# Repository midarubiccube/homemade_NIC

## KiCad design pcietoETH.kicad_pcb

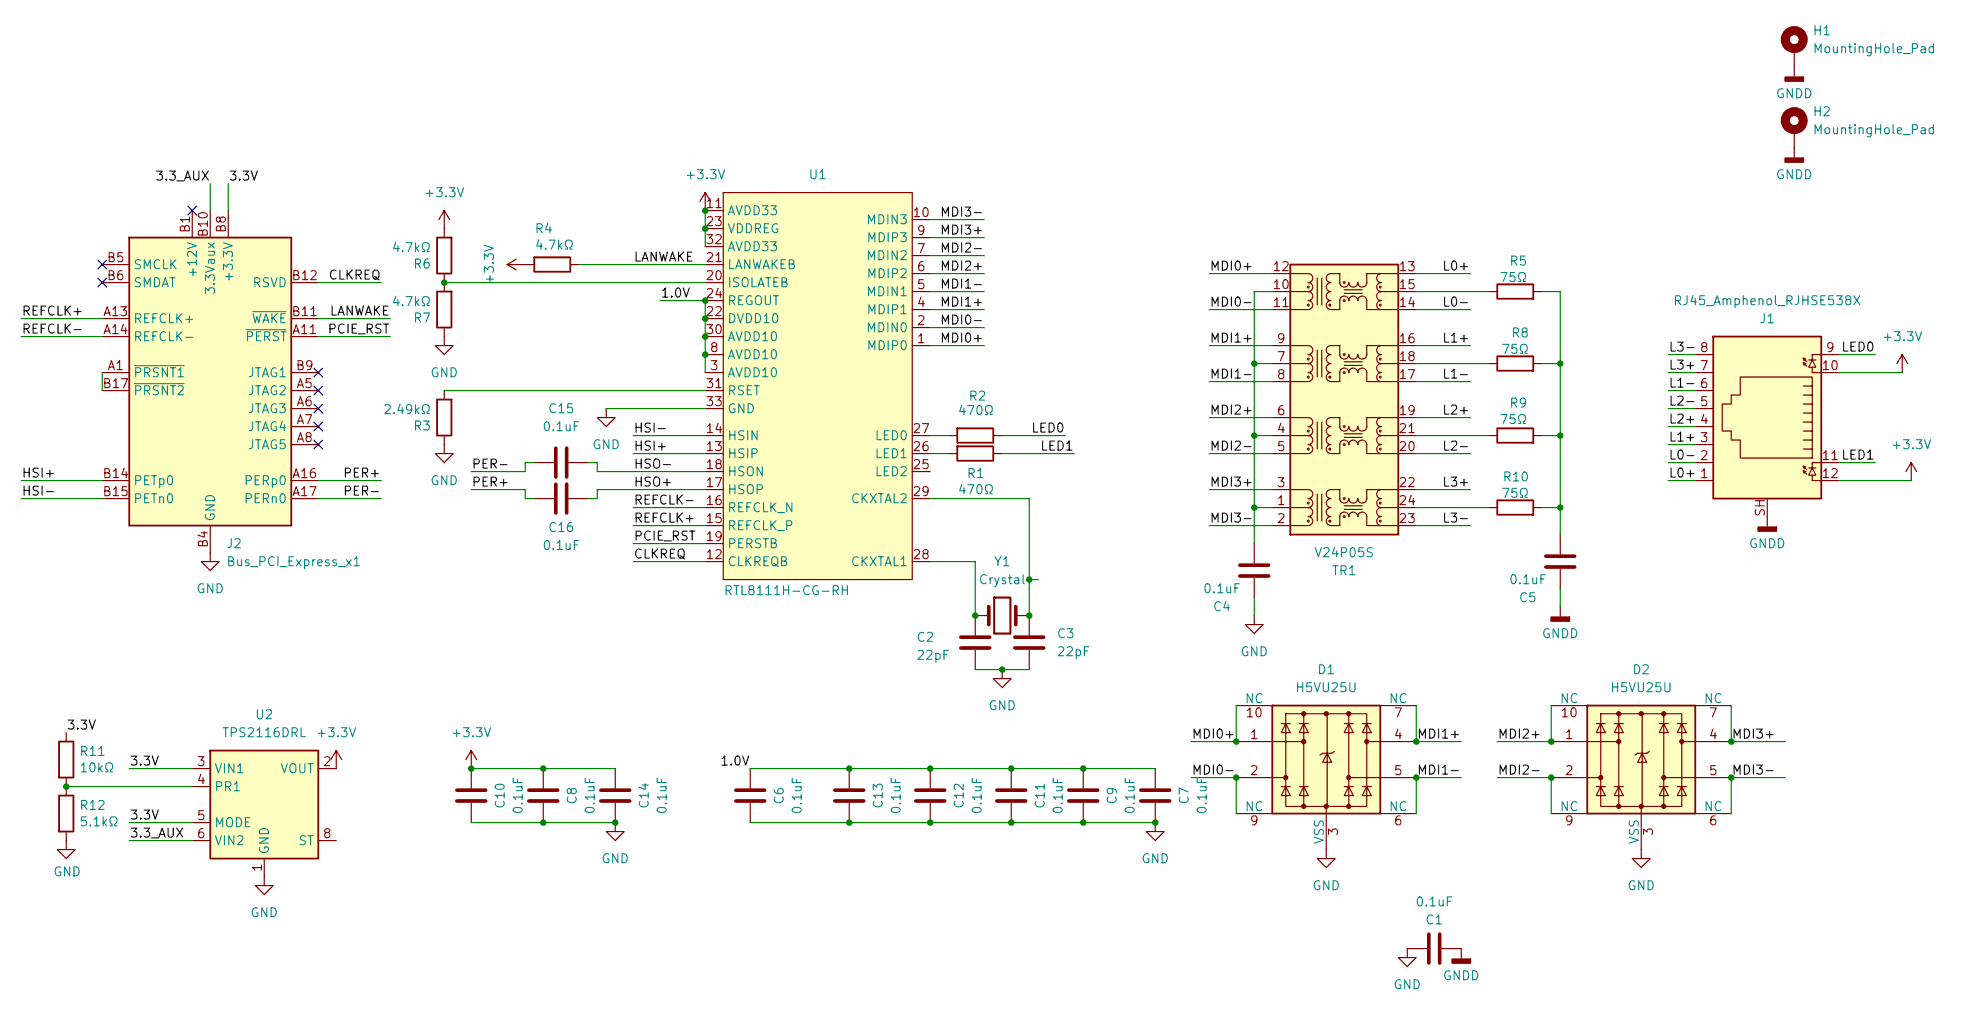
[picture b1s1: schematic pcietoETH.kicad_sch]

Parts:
C1: 0.1uF; L_1206_3216Metric_Pad1.22x1.90mm_HandSolder
C2, C3: 22pF; C_0603_1608Metric_Pad1.08x0.95mm_HandSolder
C4, C5, C6, C7, C8, C9, C10, C11, C12, C13, C14, C15, C16: 0.1uF; C_0402_1005Metric_Pad0.74x0.62mm_HandSolder
D1, D2: H5VU25U; Diodes_UDFN-10_1.0x2.5mm_P0.5mm
H1, H2: MountingHole_Pad; MountingHole_3.2mm_M3_ISO14580_Pad
J1: RJ45_Amphenol_RJHSE538X; AMPHENOL_RJSBE5381C1
J2: Bus_PCI_Express_x1; BUS_PCIexpress_x1
R1, R2: 470Ω; R_0603_1608Metric_Pad0.98x0.95mm_HandSolder; Part Description Resistor 10K M1005 1% 63mW
R3: 2.49kΩ; R_0603_1608Metric_Pad0.98x0.95mm_HandSolder; Part Description Resistor 10K M1005 1% 63mW
R4, R6, R7: 4.7kΩ; R_0603_1608Metric_Pad0.98x0.95mm_HandSolder; Part Description Resistor 10K M1005 1% 63mW
R5, R8, R9, R10: 75Ω; R_0603_1608Metric_Pad0.98x0.95mm_HandSolder; Part Description Resistor 10K M1005 1% 63mW
R11: 10kΩ; R_0603_1608Metric_Pad0.98x0.95mm_HandSolder; Part Description Resistor 2.2K M1005 1% 63mW
R12: 5.1kΩ; R_0603_1608Metric_Pad0.98x0.95mm_HandSolder; Part Description Resistor 2.2K M1005 1% 63mW
TR1: V24P05S
U1: RTL8111H-CG-RH; QFN40P400X400X90-33N
U2: TPS2116DRL; SOT-583-8
Y1: Crystal; Crystal_SMD_HC49-SD

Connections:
/1.0V: C6.2, C7.2, C9.2, C11.2, C12.2, C13.2, U1.3 (AVDD10), U1.8 (AVDD10), U1.22 (DVDD10), U1.24 (REGOUT), U1.30 (AVDD10)
/3.3_AUX: J2.B10 (3.3Vaux), U2.6 (VIN2)
/CLKREQ: J2.B12 (RSVD), U1.12 (CLKREQB)
/HSI+: J2.B14 (PETp0), U1.13 (HSIP)
/HSI-: J2.B15 (PETn0), U1.14 (HSIN)
/HSO+: C16.2, U1.17 (HSOP)
/HSO-: C15.2, U1.18 (HSON)
/L0+: J1.1, TR1.13 (MX4-)
/L0-: J1.2, TR1.14 (MX4+)
/L1+: J1.3, TR1.16 (MX3-)
/L1-: J1.6, TR1.17 (MX3+)
/L2+: J1.4, TR1.19 (MX2-)
/L2-: J1.5, TR1.20 (MX2+)
/L3+: J1.7, TR1.22 (MX1-)
/L3-: J1.8, TR1.23 (MX1+)
/LANWAKE: J2.B11 (~WAKE), R4.1, U1.21 (LANWAKEB)
/LED0: J1.9, R2.1
/LED1: J1.11, R1.1
/MDI0+: D1.1, D1.10 (NC), TR1.12 (TD4-), U1.1 (MDIP0)
/MDI0-: D1.2, D1.9 (NC), TR1.11 (TD4+), U1.2 (MDIN0)
/MDI1+: D1.4, D1.7 (NC), TR1.9 (TD3-), U1.4 (MDIP1)
/MDI1-: D1.5, D1.6 (NC), TR1.8 (TD3+), U1.5 (MDIN1)
/MDI2+: D2.1, D2.10 (NC), TR1.6 (TD2-), U1.6 (MDIP2)
/MDI2-: D2.2, D2.9 (NC), TR1.5 (TD2+), U1.7 (MDIN2)
/MDI3+: D2.4, D2.7 (NC), TR1.3 (TD1-), U1.9 (MDIP3)
/MDI3-: D2.5, D2.6 (NC), TR1.2 (TD1+), U1.10 (MDIN3)
/PCIE_RST: J2.A11 (~PERST), U1.19 (PERSTB)
/PER+: C16.1, J2.A16 (PERp0)
/PER-: C15.1, J2.A17 (PERn0)
/REFCLK+: J2.A13 (REFCLK+), U1.15 (REFCLK_P)
/REFCLK-: J2.A14 (REFCLK-), U1.16 (REFCLK_N)
GND: C1.2, C2.2, C3.2, C4.1, C6.1, C7.1, C8.1, C9.1, C10.1, C11.1, C12.1, C13.1, C14.1, D1.3 (VSS), D1.8 (VSS), D2.3 (VSS), D2.8 (VSS), J2.A4 (GND), J2.A12 (GND), J2.A15 (GND), J2.A18 (GND), J2.B4 (GND), J2.B7 (GND), J2.B13 (GND), J2.B16 (GND), J2.B18 (GND), R3.1, R7.1, R12.2, U1.33 (GND), U2.1 (GND)
GNDD: C1.1, C5.1, H1.1, H2.1, J1.SH
unnamed: C5.2, R5.2, R8.2, R9.2, R10.2
unnamed: J2.A1 (~PRSNT1), J2.B17 (~PRSNT2)
unnamed: R10.1, TR1.24 (MCT1)
unnamed: R9.1, TR1.21 (MCT2)
unnamed: R8.1, TR1.18 (MCT3)
unnamed: R5.1, TR1.15 (MCT4)
unnamed: C4.2, TR1.1 (TCT1), TR1.4 (TCT2), TR1.7 (TCT3), TR1.10 (TCT4)
unnamed: C2.1, U1.28 (CKXTAL1), Y1.1
unnamed: C3.1, U1.29 (CKXTAL2), Y1.2
unnamed: R6.1, R7.2, U1.20 (ISOLATEB)
unnamed: R2.2, U1.27 (LED0)
unnamed: R1.2, U1.26 (LED1)
unnamed: R3.2, U1.31 (RSET)
unnamed: R11.2, R12.1, U2.4 (PR1)

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
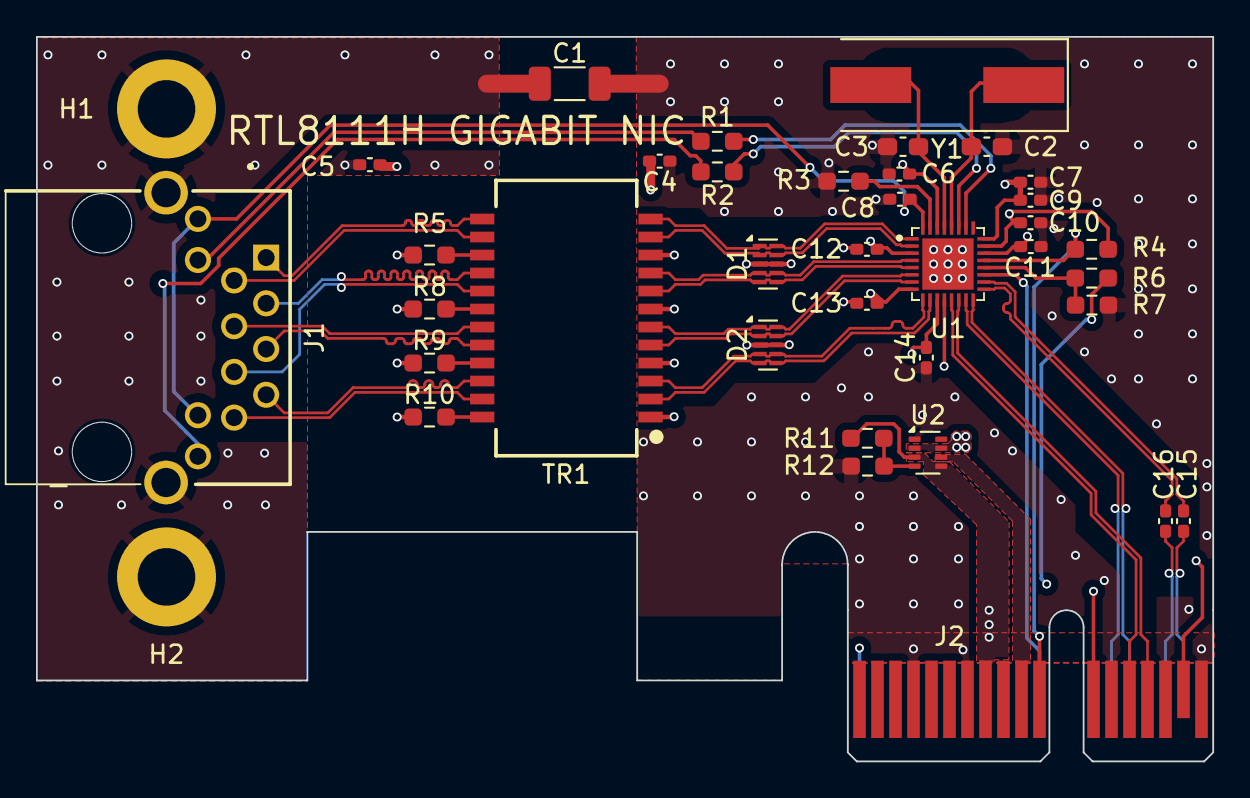
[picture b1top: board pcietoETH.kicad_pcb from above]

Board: 4 copper layers, 65.4 x 40.2 mm, 38 parts (0 on the bottom side), 49 nets.

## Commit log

2025-09-05 init commit
2025-09-05 add file
2025-09-08 Create LICENSE
2025-11-28 Add files via upload
    add pdf
